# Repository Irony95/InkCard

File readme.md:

# Introduction
An e-ink display card that mirrors your phone screen, to help with reading documents, e-books, web pages etc!

The project is made to be as cheap as possible, coming to a total cost of around $35USD for materials. This would be even lower if made/bought in bulk!

As this is a prototype and in heavy development, I would not recommend making this unless you're willing to tinker/is familiar with electronics and or app dev.
Nevertheless, If you do want to make the project you are free to do so! I am open to answering any questions should you make the card.
I am also open to the idea of making and selling the hardware itself, though this comes down to if there is interest in the project and when I feel the quality is good enough.

Currently, there is only support for an android app. Check out the repo [here](https://github.com/Irony95/InkCard-androidApp).
I have no experience in IOS development, so I am entirely unsure if an app can even be made for the IOS system. If it is, do let me know!

Any suggestions and support is greatly welcomed.

### Notes when building
1. Use a 11uH receiver coil and connect to AC1 and AC2. feel free to use a different coil if you so wish, with C32-C34 and C15 for tuning. refer to BQ51013 datasheet for more info
2. Bridge both JP1 and JP3 from the middle to pad 3, these help select options for the e-paper driver
3. Adjust/remake the CoilLifter.stl to fit your receiver coil size

### Glam Pics!

### Future 
Although the project was primarily built to be as cheap as possible so to allow anybody to get an e-reader, a future version with touch screen and battery is being considered! This version would likely add significant amounts to the cost, but would likely make the project infinitely better. 
Additional features like auto/partial screen refreshes, manual cropping, custom button functions are also being considered.

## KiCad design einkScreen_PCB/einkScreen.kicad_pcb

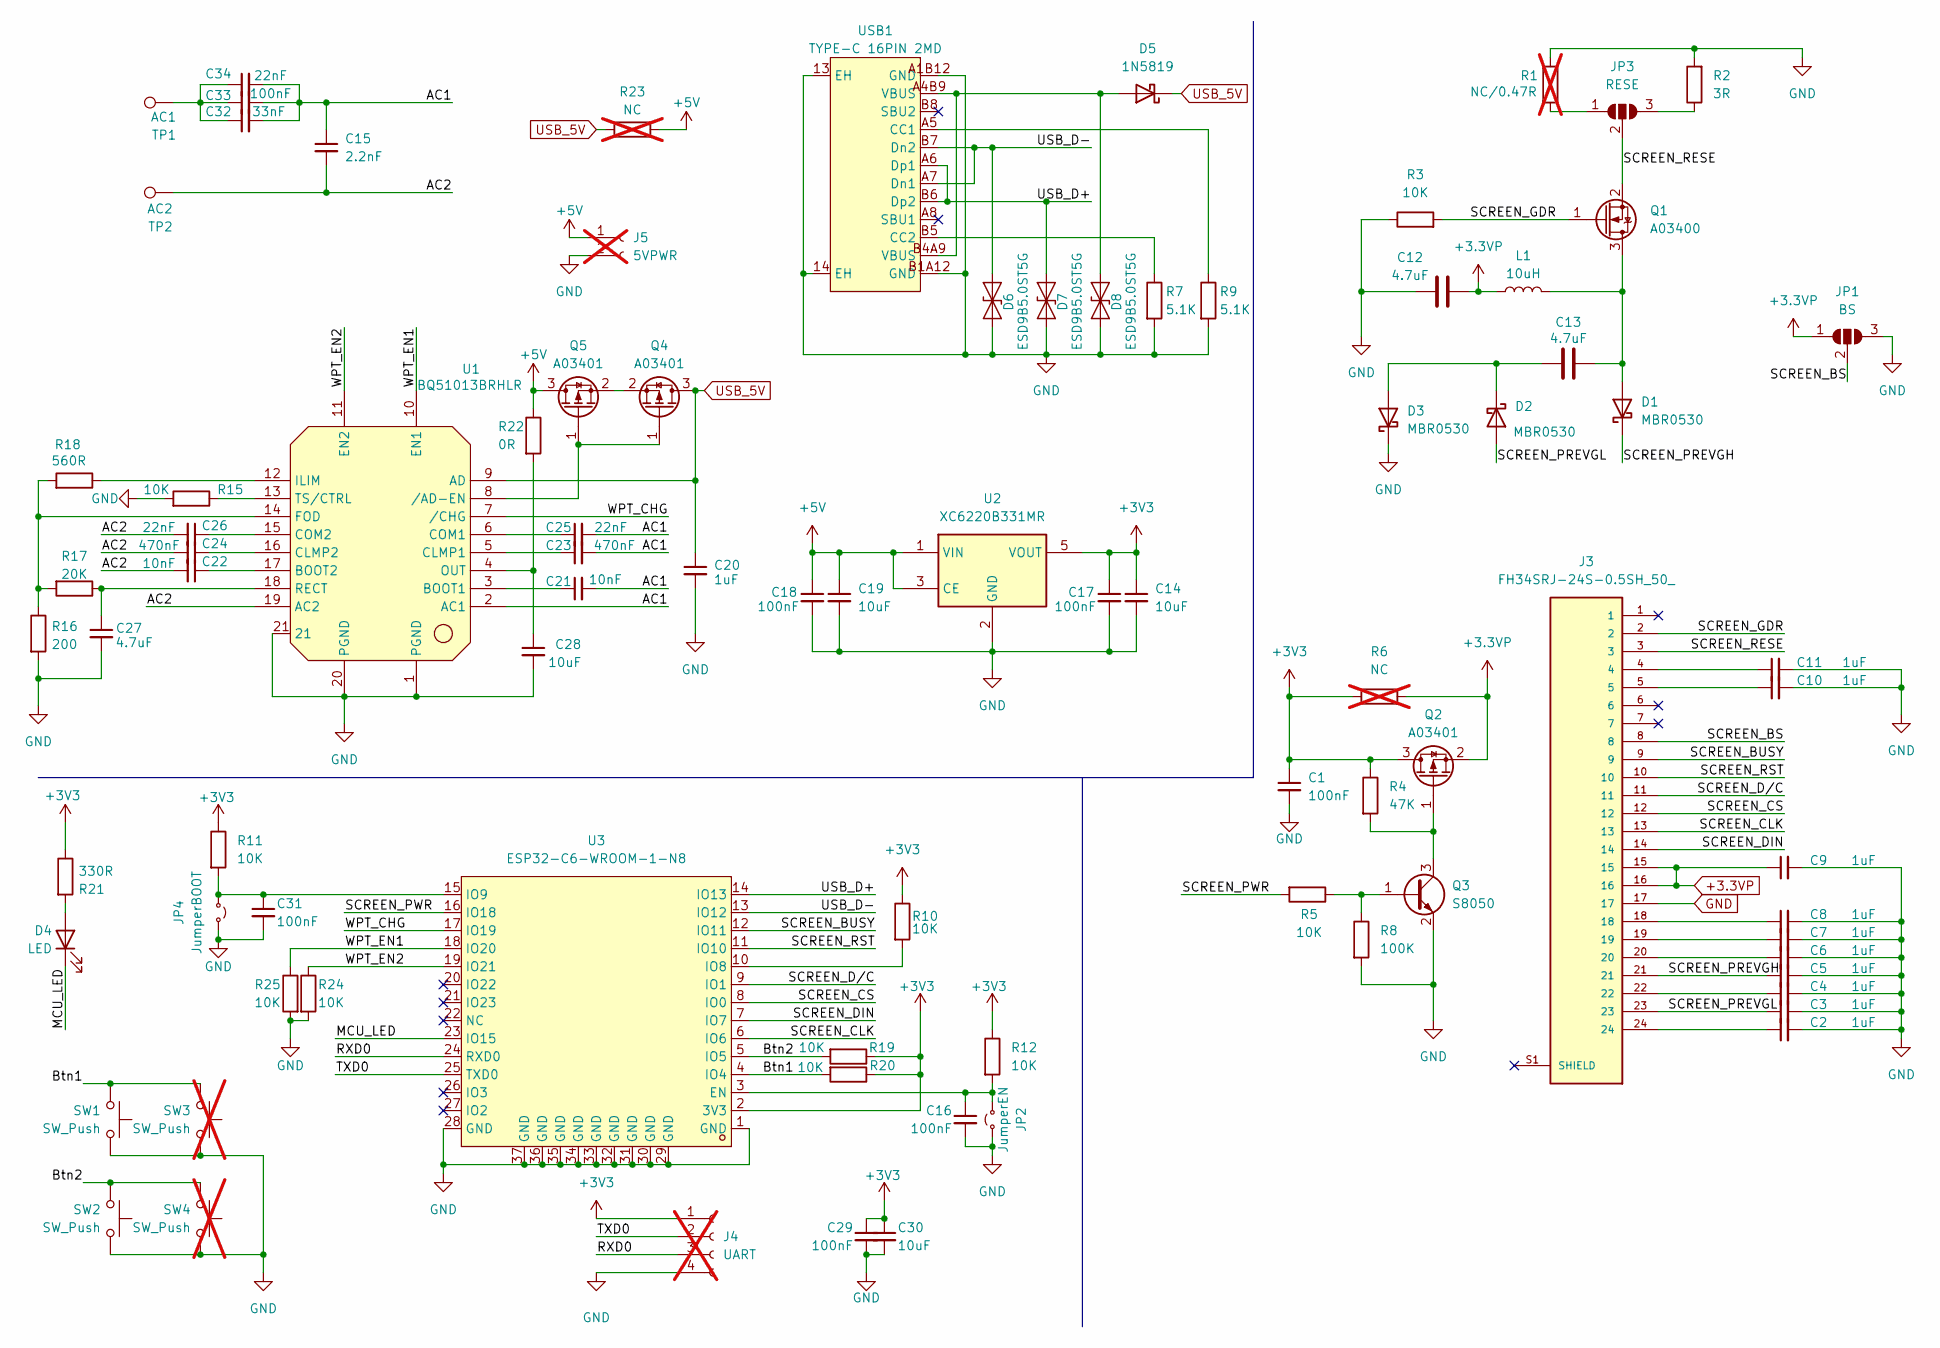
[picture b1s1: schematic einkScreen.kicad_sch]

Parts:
C1, C16, C17, C18, C29, C31, C33: 100nF; C_0805_2012Metric; LCSC C28233
C2, C3, C4, C5, C6, C7, C8, C9, C10, C11, C20: 1uF; C_0805_2012Metric; LCSC C28323
C12, C13, C27: 4.7uF; C_0805_2012Metric; LCSC C1779
C14, C19, C28, C30: 10uF; C_0805_2012Metric; LCSC C15850
C15: 2.2nF; C_0805_2012Metric; LCSC C28260
C21, C22: 10nF; C_0805_2012Metric; LCSC C1710
C23, C24: 470nF; C_0805_2012Metric; LCSC C13967
C25, C26, C34: 22nF; C_0805_2012Metric; LCSC C1729
C32: 33nF; C_0805_2012Metric; LCSC C1739
D1, D2, D3: MBR0530; D_SOD-123; LCSC C18863
D4: LED; LED_0805_2012Metric; LCSC C84256
D5: 1N5819; D_SOD-123; LCSC C82544
D6, D7, D8: ESD9B5.0ST5G; D_SOD-923; LCSC C111566
J3: FH34SRJ-24S-0.5SH_50_; HRS_FH34SRJ-24S-0.5SH_50_; LCSC C324726
J4: UART; PinSocket_1x04_P2.54mm_Vertical; not fitted
J5: 5VPWR; PinSocket_1x02_P2.54mm_Vertical; not fitted
JP1: BS; SolderJumper-3_P1.3mm_Open_RoundedPad1.0x1.5mm_NumberLabels
JP2: JumperEN; TestPoint_2Pads_Pitch2.54mm_Drill0.8mm
JP3: RESE; SolderJumper-3_P1.3mm_Open_RoundedPad1.0x1.5mm_NumberLabels
JP4: JumperBOOT; TestPoint_2Pads_Pitch2.54mm_Drill0.8mm
L1: 10uH; L_1210_3225Metric; LCSC C60541
Q1: A03400; TSOT-23; LCSC C20917
Q2, Q4, Q5: A03401; TSOT-23; LCSC C15127
Q3: S8050; TSOT-23; LCSC C2146
R1: NC/0.47R; R_0805_2012Metric; not fitted
R2: 3R; R_0805_2012Metric; LCSC C17660
R3, R5, R10, R11, R12, R15, R19, R20, R24, R25: 10K; R_0805_2012Metric; LCSC C17414
R4: 47K; R_0805_2012Metric; LCSC C17713
R6, R23: NC; R_0805_2012Metric; not fitted
R7, R9: 5.1K; R_0805_2012Metric; LCSC C27834
R8: 100K; R_0805_2012Metric; LCSC C149504
R16: 200; R_0805_2012Metric; LCSC C17540
R17: 20K; R_0805_2012Metric; LCSC C4328
R18: 560R; R_0805_2012Metric; LCSC C28636
R21: 330R; R_0805_2012Metric; LCSC C17630
R22: 0R; R_0805_2012Metric; LCSC C17477
SW1, SW2: SW_Push; Panasonic_EVQPUL_EVQPUC; LCSC C79174
SW3, SW4: SW_Push; KEY-SMD_L4.0-W3.0-LS4.9-1; not fitted
TP1: AC1; TestPoint_Pad_D3.0mm
TP2: AC2; TestPoint_Pad_D3.0mm
U1: BQ51013BRHLR; VQFN-20_L4.5-W3.5-P0.50-BL-EP_BQ24100RHLR; MPN BQ51013BRHLR; LCSC Part C55663
U2: XC6220B331MR; SOT-23-5; LCSC C22466451
U3: ESP32-C6-WROOM-1-N8; WIRELM-SMD_ESP32-C6-WROOM-1; MPN ESP32-C6-WROOM-1-N8; LCSC Part C5366877
USB1: TYPE-C 16PIN 2MD; USB-C-SMD_TYPE-C-16PIN-2MD-073; MPN TYPE-C 16PIN 2MD(073); LCSC Part C2765186

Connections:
+3.3VP: C9.1, C12.2, J3.15, J3.16, JP1.1 (A), L1.1, Q2.2 (S), R6.2
+3V3: C1.1, C14.1, C17.1, C29.1, C30.1, J4.1, Q2.3 (D), R4.1, R6.1, R10.1, R11.1, R12.1, R19.1, R20.1, R21.1, U2.5 (VOUT), U3.2 (3V3)
+5V: C18.1, C19.1, J5.1, Q5.3 (D), R22.1, R23.2, U2.1 (VIN), U2.3 (CE)
/AC1: C15.1, C21.2, C23.2, C25.2, C32.2, C33.2, C34.2, U1.2 (AC1)
/AC2: C15.2, C22.2, C24.2, C26.2, TP2.1 (1_1), U1.19 (AC2)
/Btn1: R20.2, SW1.2, SW3.2, U3.4 (IO4)
/Btn2: R19.2, SW2.2, SW4.2, U3.5 (IO5)
/MCU_LED: D4.1 (K), U3.23 (IO15)
/RXD0: J4.3, U3.24 (RXD0)
/SCREEN_BS: J3.8, JP1.2 (C)
/SCREEN_BUSY: J3.9, U3.12 (IO11)
/SCREEN_CLK: J3.13, U3.6 (IO6)
/SCREEN_CS: J3.12, U3.8 (IO0)
/SCREEN_DIN: J3.14, U3.7 (IO7)
/SCREEN_D/C: J3.11, U3.9 (IO1)
/SCREEN_GDR: J3.2, Q1.1 (G), R3.2
/SCREEN_PREVGH: C5.1, D1.1 (K), J3.21
/SCREEN_PREVGL: C3.1, D2.2 (A), J3.23
/SCREEN_PWR: R5.2, U3.16 (IO18)
/SCREEN_RESE: J3.3, JP3.2 (C), Q1.2 (S)
/SCREEN_RST: J3.10, U3.11 (IO10)
/TXD0: J4.2, U3.25 (TXD0)
/USB_D+: D7.2 (A2), U3.14 (IO13), USB1.A6 (Dp1), USB1.B6 (Dp2)
/USB_D-: D6.2 (A2), U3.13 (IO12), USB1.A7 (Dn1), USB1.B7 (Dn2)
/WPT_CHG: U1.7 (/CHG), U3.17 (IO19)
/WPT_EN1: R25.1, U1.10 (EN1), U3.18 (IO20)
/WPT_EN2: R24.1, U1.11 (EN2), U3.19 (IO21)
GND: C1.2, C2.2, C3.2, C4.2, C5.2, C6.2, C7.2, C8.2, C9.2, C10.2, C11.2, C12.1, C14.2, C16.2, C17.2, C18.2, C19.2, C20.2, C27.2, C28.2, C29.2, C30.2, C31.2, D3.1 (K), D6.1 (A1), D7.1 (A1), D8.1 (A1), J3.17, J4.4, J5.2, JP1.3 (B), JP2.2 (B), JP4.2 (B), Q3.2 (E), R1.1, R2.2, R3.1, R7.2, R8.2, R9.2, R15.2, R16.2, R24.2, R25.2, SW1.1, SW2.1, SW3.1, SW4.1, U1.1 (PGND), U1.20 (PGND), U1.21, U2.2 (GND), U3.1 (GND), U3.28 (GND), U3.29 (GND), U3.30 (GND), U3.31 (GND), U3.32 (GND), U3.33 (GND), U3.34 (GND), U3.35 (GND), U3.36 (GND), U3.37 (GND), USB1.13 (EH), USB1.14 (EH), USB1.A1B12 (GND), USB1.B1A12 (GND)
unnamed: C2.1, J3.24
unnamed: C4.1, J3.22
unnamed: C6.1, J3.20
unnamed: C7.1, J3.19
unnamed: C8.1, J3.18
unnamed: C10.1, J3.5
unnamed: C11.1, J3.4
unnamed: C32.1, C33.1, C34.1, TP1.1 (1_1)
unnamed: C13.2, D1.2 (A), L1.2, Q1.3 (D)
unnamed: C13.1, D2.1 (K), D3.2 (A)
unnamed: D4.2 (A), R21.2
unnamed: D5.2 (A), D8.2 (A2), USB1.A4B9 (VBUS), USB1.B4A9 (VBUS)
unnamed: C16.1, JP2.1 (A), R12.2, U3.3 (EN)
unnamed: JP3.1 (A), R1.2
unnamed: JP3.3 (B), R2.1
unnamed: C31.1, JP4.1 (A), R11.2, U3.15 (IO9)
unnamed: Q2.1 (G), Q3.3 (C), R4.2
unnamed: Q3.1 (B), R5.1, R8.1
unnamed: Q4.1 (G), Q5.1 (G), U1.8 (/AD-EN)
unnamed: Q4.2 (S), Q5.2 (S)
unnamed: C21.1, U1.3 (BOOT1)
unnamed: C22.1, U1.17 (BOOT2)
unnamed: C23.1, U1.5 (CLMP1)
unnamed: C24.1, U1.16 (CLMP2)
unnamed: C25.1, U1.6 (COM1)
unnamed: C26.1, U1.15 (COM2)
unnamed: R16.1, R17.2, R18.2, U1.14 (FOD)
unnamed: R18.1, U1.12 (ILIM)
unnamed: C28.1, R22.2, U1.4 (OUT)
unnamed: C27.1, R17.1, U1.18 (RECT)
unnamed: R15.1, U1.13 (TS/CTRL)
unnamed: R10.2, U3.10 (IO8)
unnamed: R9.1, USB1.A5 (CC1)
unnamed: R7.1, USB1.B5 (CC2)
USB_5V: C20.1, D5.1 (K), Q4.3 (D), R23.1, U1.9 (AD)

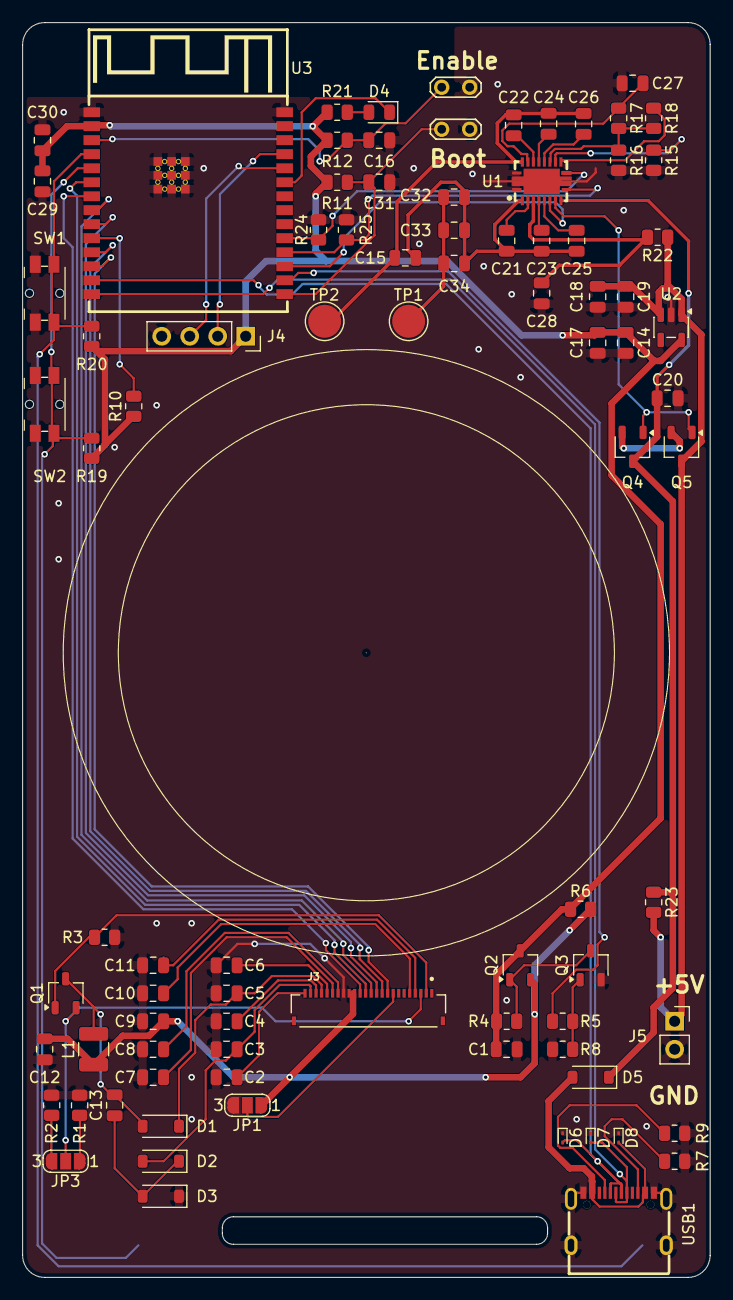
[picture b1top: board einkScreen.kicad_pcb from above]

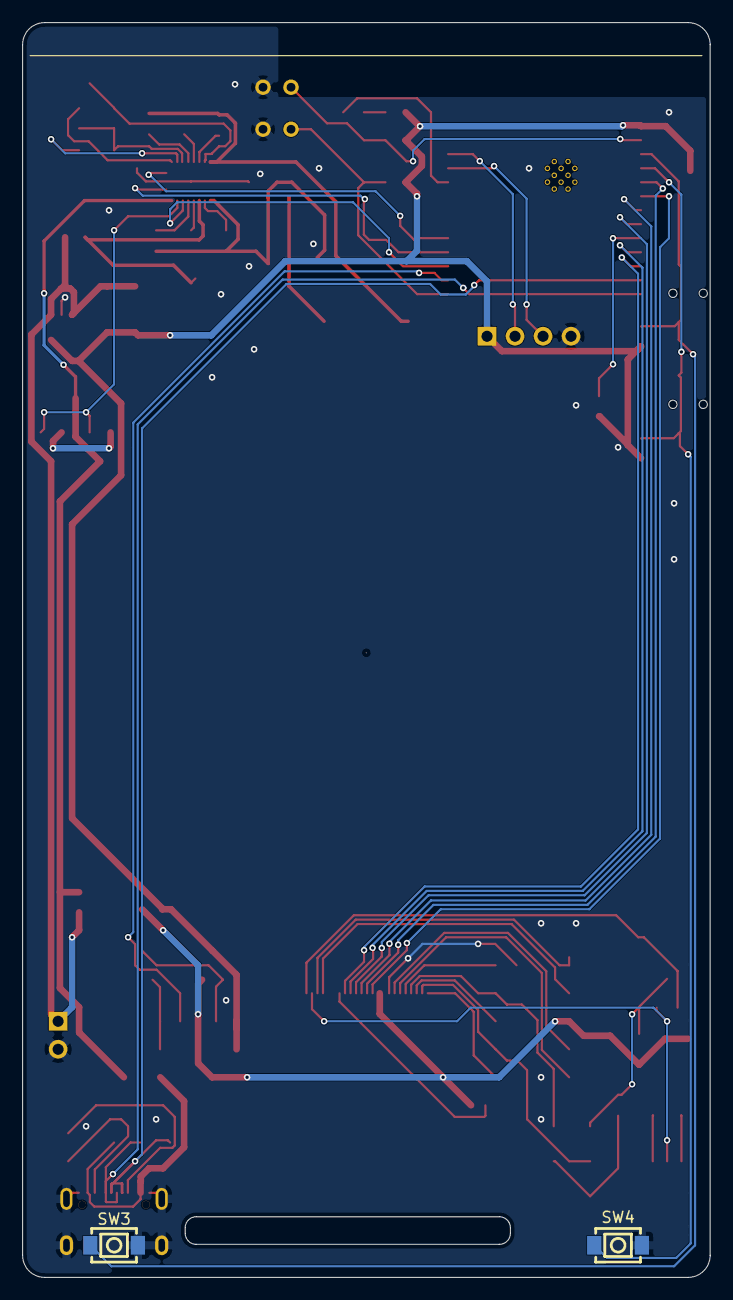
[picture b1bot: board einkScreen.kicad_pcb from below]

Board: 2 copper layers, 62.4 x 113.8 mm, 88 parts (2 on the bottom side), 63 nets.

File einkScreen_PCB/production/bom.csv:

Designator,Footprint,Quantity,Value,LCSC Part #
"C1, C16, C17, C18, C29, C31, C33",0805,7,100nF,C28233
"C10, C11, C2, C20, C3, C4, C5, C6, C7, C8, C9",0805,11,1uF,C28323
"C12, C13, C27",0805,3,4.7uF,C1779
"C14, C19, C28, C30",0805,4,10uF,C15850
C15,0805,1,2.2nF,C28260
"C21, C22",0805,2,10nF,C1710
"C23, C24",0805,2,470nF,C13967
"C25, C26, C34",0805,3,22nF,C1729
C32,0805,1,33nF,C1739
"D1, D2, D3",D_SOD-123,3,MBR0530,C18863
D4,0805,1,LED,C84256
D5,D_SOD-123,1,1N5819,C82544
"D6, D7, D8",D_SOD-923,3,ESD9B5.0ST5G,C111566
J3,HRS_FH34SRJ-24S-0.5SH_50_,1,FH34SRJ-24S-0.5SH_50_,C324726
JP2,TestPoint_2Pads_Pitch2.54mm_Drill0.8mm,1,JumperEN,
JP4,TestPoint_2Pads_Pitch2.54mm_Drill0.8mm,1,JumperBOOT,
L1,1210,1,10uH,C60541
Q1,TSOT-23,1,A03400,C20917
"Q2, Q4, Q5",TSOT-23,3,A03401,C15127
Q3,TSOT-23,1,S8050,C2146
"R10, R11, R12, R15, R19, R20, R24, R25, R3, R5",0805,10,10K,C17414
R16,0805,1,200,C17540
R17,0805,1,20K,C4328
R18,0805,1,560R,C28636
R2,0805,1,3R,C17660
R21,0805,1,330R,C17630
R22,0805,1,0R,C17477
R4,0805,1,47K,C17713
"R7, R9",0805,2,5.1K,C27834
R8,0805,1,100K,C149504
"SW1, SW2",Panasonic_EVQPUL_EVQPUC,2,SW_Push,C79174
TP1,TestPoint_Pad_D3.0mm,1,AC1,
TP2,TestPoint_Pad_D3.0mm,1,AC2,
U1,VQFN-20_L4.5-W3.5-P0.50-BL-EP_BQ24100RHLR,1,BQ51013BRHLR,C55663
U2,SOT-23-5,1,XC6220B331MR,C22466451
U3,WIRELM-SMD_ESP32-C6-WROOM-1,1,ESP32-C6-WROOM-1-N8,C5366877
USB1,USB-C-SMD_TYPE-C-16PIN-2MD-073,1,TYPE-C 16PIN 2MD,C2765186

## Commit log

2026-04-18 nfc version
2026-05-25 working BLE
2026-06-02 working kinda
2026-06-20 still working
2026-06-23 fixed card issues
2026-06-23 added simple readme.md file
2026-06-23 Update readme.md with some pics
2026-06-23 Update readme styling
2026-06-24 deleted Platform IO version, too lazy to configure
